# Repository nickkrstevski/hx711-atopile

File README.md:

# hx711

Wooohooo a new package!

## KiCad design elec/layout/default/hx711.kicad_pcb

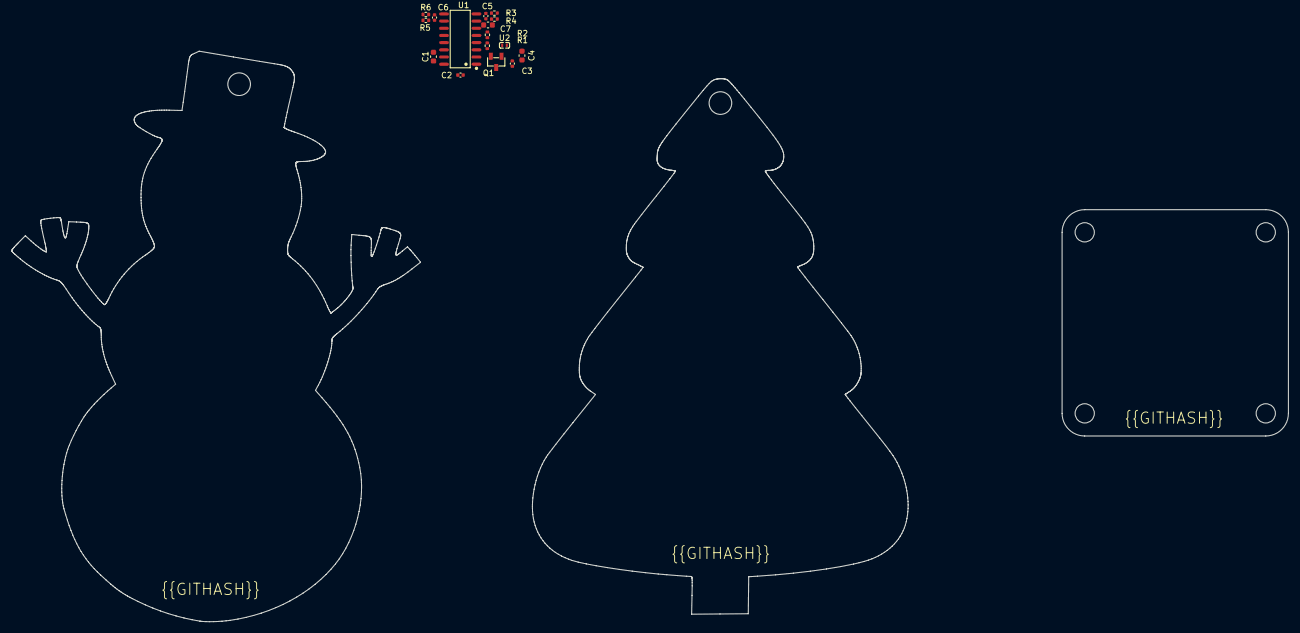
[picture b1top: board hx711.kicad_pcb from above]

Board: 2 copper layers, 16 parts (0 on the bottom side), 11 nets, no tracks yet.

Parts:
C1, C4, C7: 50V 100nF X7R ±10% 0603 Multilayer Ceramic Capaci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; C0603
C2, C3: 6.3V 10uF X5R ±20% 0402 Multilayer Ceramic Capaci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; C0402
C5, C6: 16V 100nF X7R ±10% 0402 Multilayer Ceramic Capaci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; C0402
Q1: SOT-23-3_L2.9-W1.3-P1.90-LS2.4-BR
R1: 62.5mW Thick Film Resistors ±100ppm/℃ ±1% 10kΩ 04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; R0402
R2: 62.5mW Thick Film Resistors ±100ppm/℃ ±1% 8.2kΩ 0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; R0402
R3, R4, R5, R6: 62.5mW Thick Film Resistors ±1% ±200ppm/℃ 100Ω 04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; R0402
U1: SOP-16_L10.0-W3.9-P1.27-LS6.0-BL
U2: 3.3 +/- 0.99 (30%) microhenry; IND-SMD_L1.2-W0.7

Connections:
base: Q1.1, U1.2
gnd: C1.2, C2.2, C3.2, C4.2, C7.2, R2.2, U1.5, U1.14
ic-vcc: C1.1, C2.1, Q1.3, U1.1, U1.16
ic-vcc-1: Q1.2, R1.1, U1.3, U2.1
inna: C5.2, R3.2, U1.7
innb: C6.2, R5.2, U1.9
inpa: C5.1, R4.2, U1.8
inpb: C6.1, R6.2, U1.10
vbg: C7.1, U1.6
vcc: C3.1, C4.1, U2.2
vfb: R1.2, R2.1, U1.4

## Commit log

2024-02-13 Configure project
2024-02-13 updating module
2024-02-14 connect force gnd to power gnd
2024-03-28 manually selecting inductor
2024-04-02 fixed emitter collector mixup
